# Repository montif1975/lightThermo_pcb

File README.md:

# lightThermo_pcb
PCB carrier board for lightThermo, based on Raspberry PICO.

Schematic, PCB and construction files (gerber) for PBC carrier for lightThermo but can be used to connect generic I2C add-on on Raspberry PICO.

The project contains two folders:
- lightThermo is the schematic and PCB for single device
- lightThermo_panel is the multi-PCB construction file (2 PCB in a single frame)

The project is made with KiCad 9.0.

The resulting PCB is:

The multi-PCB frame is:

I printed and assembled some samples, here the PCB (without the PICO and the I2C devices):

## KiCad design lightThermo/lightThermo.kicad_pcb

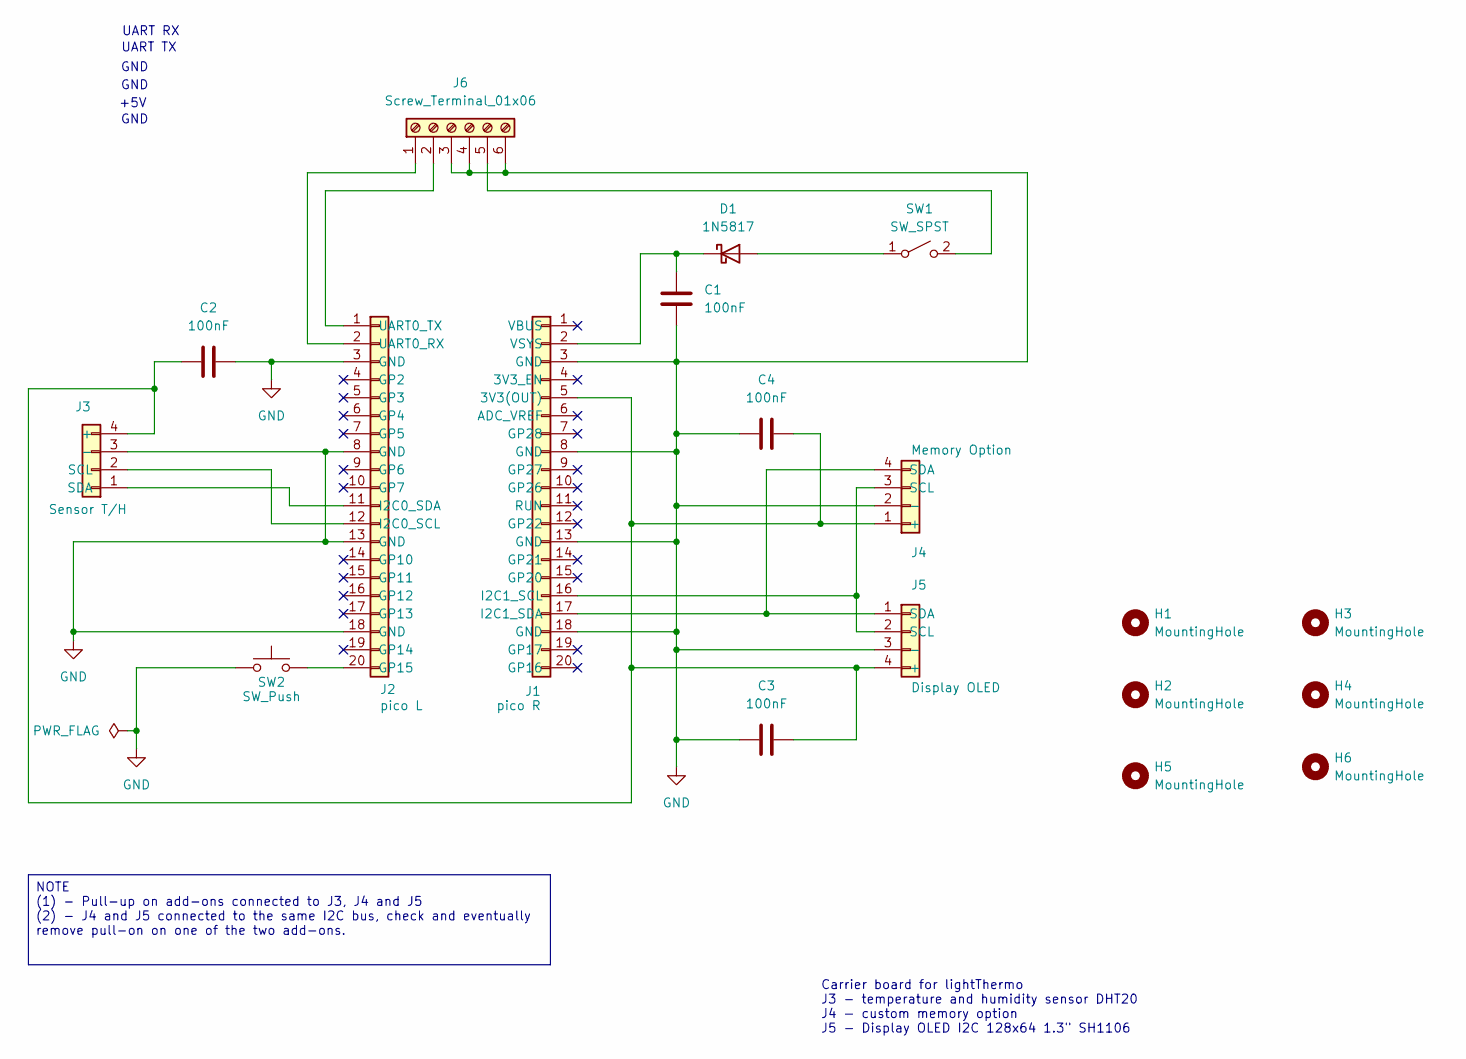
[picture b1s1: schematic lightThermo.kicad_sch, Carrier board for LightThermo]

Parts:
C1, C2, C3, C4: 100nF; C_Disc_D3.0mm_W2.0mm_P2.50mm
D1: 1N5817; D_DO-41_SOD81_P10.16mm_Horizontal
H1, H2, H3, H4, H5, H6: MountingHole; MountingHole_3.2mm_M3
J1: pico R; PinSocket_1x20_P2.54mm_Vertical
J2: pico L; PinSocket_1x20_P2.54mm_Vertical
J3: Sensor T/H; PinSocket_1x04_P2.54mm_Vertical
J4: Memory Option; PinSocket_1x04_P2.54mm_Vertical
J5: Display OLED; PinSocket_1x04_P2.54mm_Vertical
J6: Screw_Terminal_01x06; TerminalBlock_Phoenix_PT-1,5-6-5.0-H_1x06_P5.00mm_Horizontal
SW1: SW_SPST; SW_Slide_SPDT_Straight_CK_OS102011MS2Q
SW2: SW_Push; SW_PUSH_6mm_H8mm

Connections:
GND: C1.1, C2.1, C3.2, C4.2, J1.3 (GND), J1.8 (GND), J1.13 (GND), J1.18 (GND), J2.3 (GND), J2.8 (GND), J2.13 (GND), J2.18 (GND), J3.3 (-), J4.2 (-), J5.3 (-), J6.3, J6.4, J6.6, SW2.1
unnamed: D1.2 (A), SW1.1 (A)
unnamed: C1.2, D1.1 (K), J1.2 (VSYS)
unnamed: C2.2, C3.1, C4.1, J1.5 (3V3(OUT)), J3.4 (+), J4.1 (+), J5.4 (+)
unnamed: J1.16 (I2C1_SCL), J4.3 (SCL), J5.2 (SCL)
unnamed: J1.17 (I2C1_SDA), J4.4 (SDA), J5.1 (SDA)
unnamed: J2.20 (GP15), SW2.2
unnamed: J2.12 (I2C0_SCL), J3.2 (SCL)
unnamed: J2.11 (I2C0_SDA), J3.1 (SDA)
unnamed: J2.2 (UART0_RX), J6.1
unnamed: J2.1 (UART0_TX), J6.2
unnamed: J6.5, SW1.2 (B)

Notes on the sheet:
GND
UART RX
Carrier board for lightThermo J3 - temperature and humidity sensor DHT20 J4 - custom memory option J5 - Display OLED I2C 128x64 1.3" SH1106
UART TX
+5V
NOTE (1) - Pull-up on add-ons connected to J3, J4 and J5 (2) - J4 and J5 connected to the same I2C bus, check and eventually remove pull-on on one of the two add-ons.

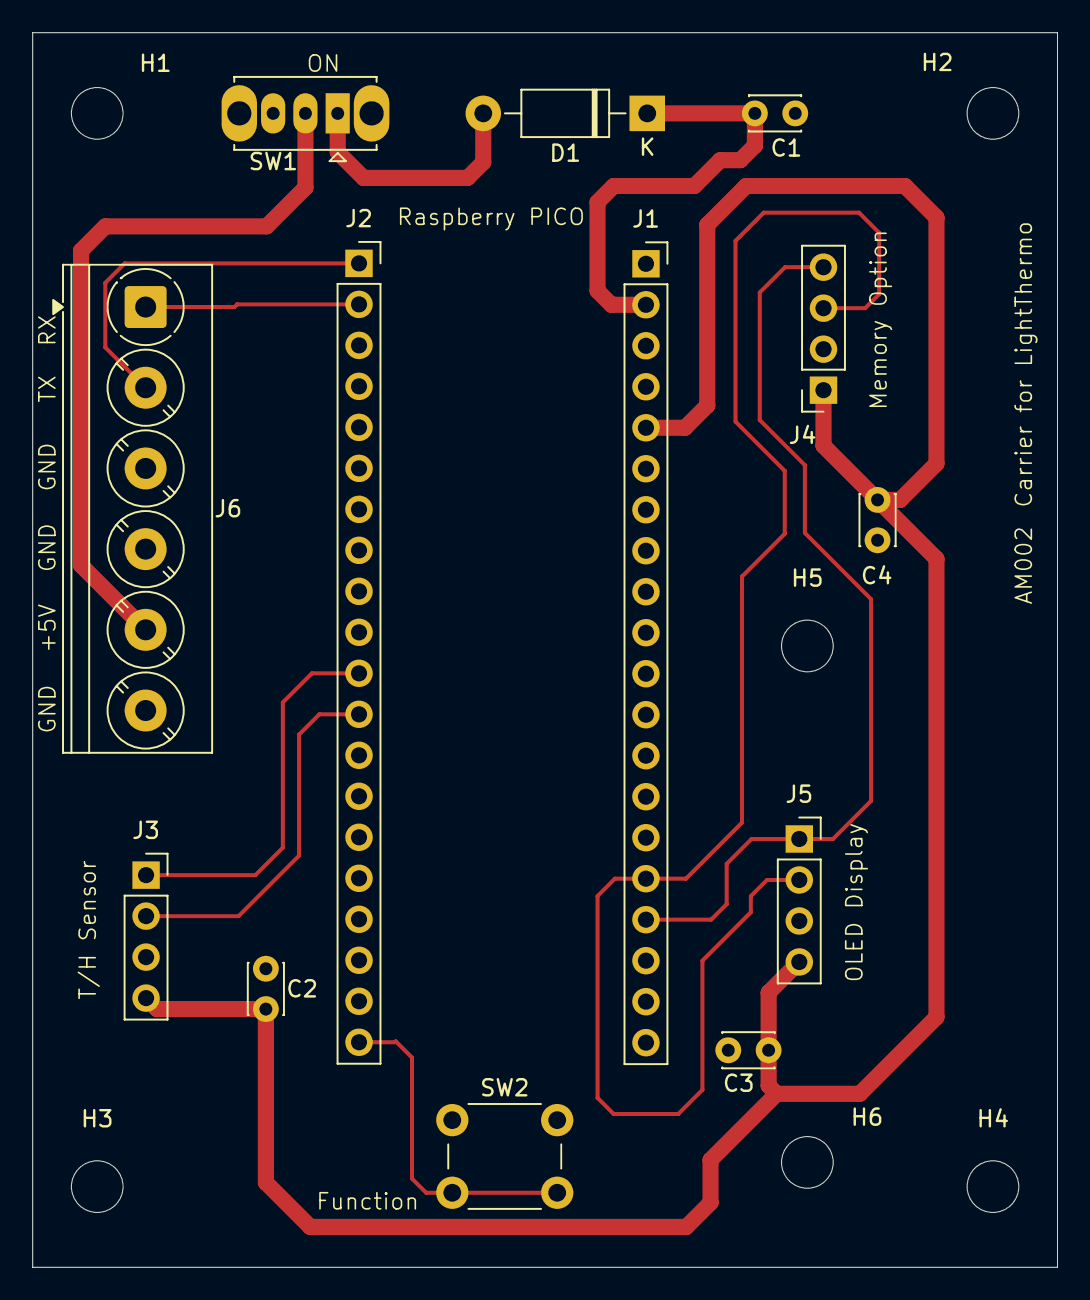
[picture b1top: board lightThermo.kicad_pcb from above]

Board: 2 copper layers, 63.5 x 76.5 mm, 19 parts (0 on the bottom side), 12 nets.

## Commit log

2025-03-16 Add files via upload
    First commit
2025-05-03 Updated README and add a picture of the PCB assembled.
